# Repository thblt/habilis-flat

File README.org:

#+TITLE: Yet another keyboard

A keyboard, nothing exceptional.  This is mostly an intermediate step
for layout-testing the [[https://github.com/thblt/habilis][Habilis]].

Schematic and PCB (KiCad 7) are in =pcb/=, firmware lives in =fw/=.
The firmware is QMK, so should be symlinked in the correct location:

#+begin_example
ln -s ~/PATH/TO/REPO/habilis-flat/fw ~/qmk_firmware/keyboards/habilis-flat
#+end_example

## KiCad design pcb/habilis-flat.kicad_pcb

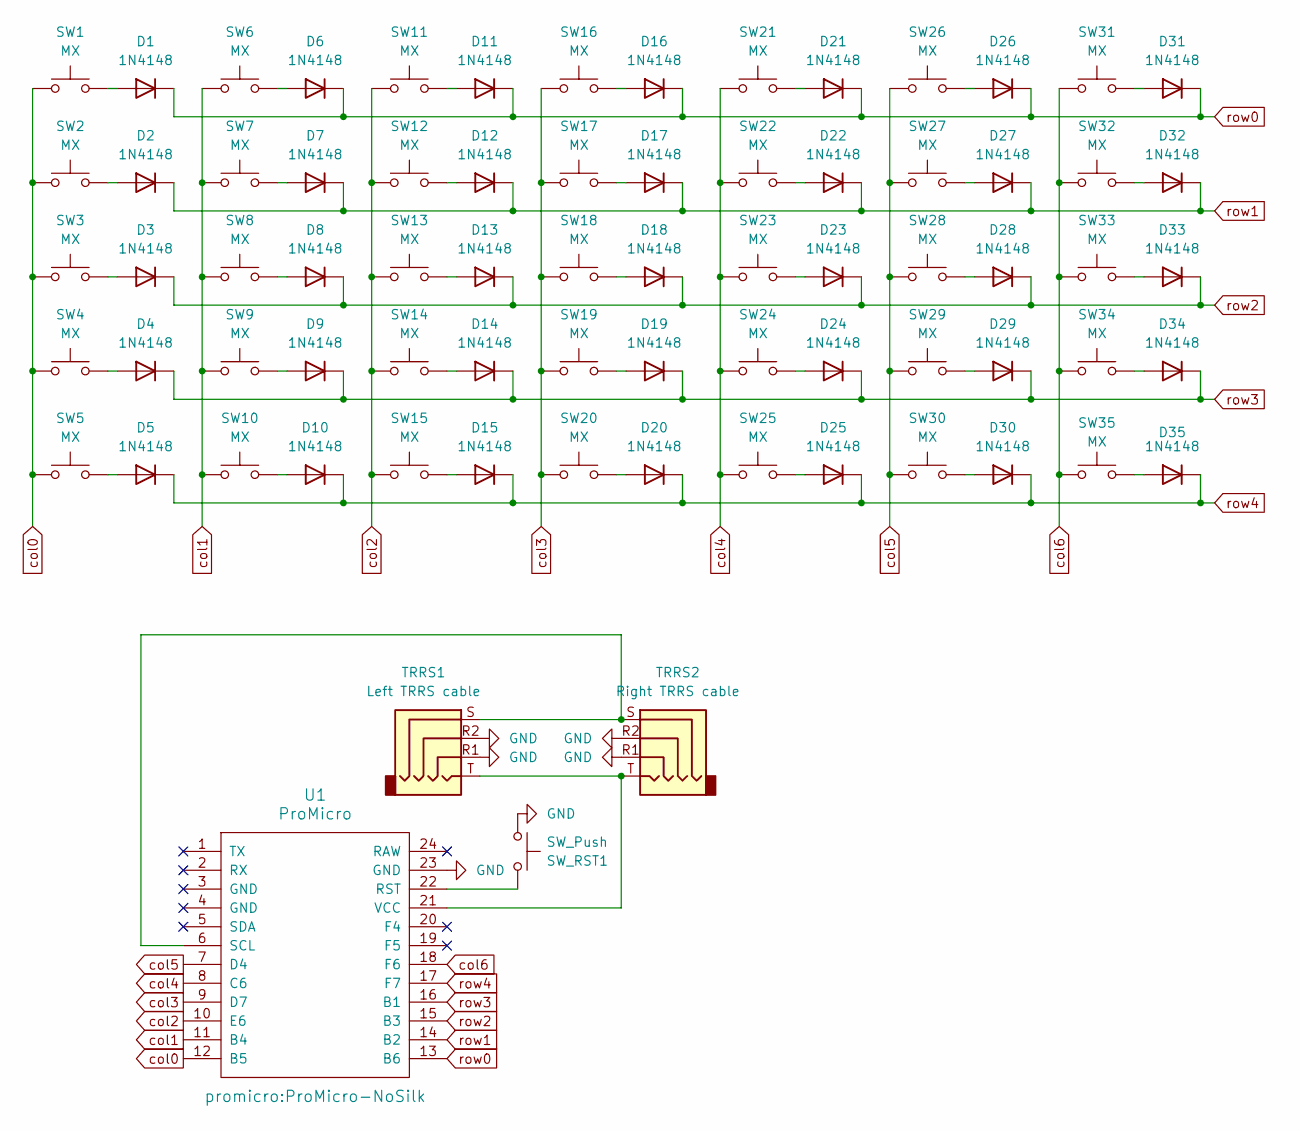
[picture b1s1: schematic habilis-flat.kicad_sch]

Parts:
D1, D2, D3, D4, D5, D6, D7, D8, D9, D10, D11, D12, D13, D14, D15, D16, D17, D18, D19, D20, D21, D22, D23, D24, D25, D26, D27, D28, D29, D30, D31, D32, D33, D34, D35: 1N4148; D_DO-35_SOD27_P7.62mm_Horizontal
SW1, SW2, SW3, SW4, SW5, SW6, SW7, SW8, SW9, SW10, SW11, SW12, SW13, SW14, SW15, SW16, SW17, SW18, SW19, SW20, SW21, SW22, SW23, SW24, SW25, SW26, SW27, SW28, SW29, SW30, SW31, SW32, SW33, SW34, SW35: MX; SW_MX_reversible_decentered
SW_RST1: SW_Push; that_push_button_i_have_in_stock
TRRS1: Left TRRS cable; Jack breakout board
TRRS2: Right TRRS cable; Jack breakout board
U1: ProMicro; ProMicro-NoSilk

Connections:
GND: SW_RST1.2, TRRS1.R1, TRRS1.R2, TRRS2.R1, TRRS2.R2, U1.23 (GND)
unnamed: D1.2 (A), SW1.1
unnamed: D2.2 (A), SW2.1
unnamed: D3.2 (A), SW3.1
unnamed: D4.2 (A), SW4.1
unnamed: D5.2 (A), SW5.1
unnamed: D6.2 (A), SW6.1
unnamed: D7.2 (A), SW7.1
unnamed: D8.2 (A), SW8.1
unnamed: D9.2 (A), SW9.1
unnamed: D10.2 (A), SW10.1
unnamed: D11.2 (A), SW11.1
unnamed: D12.2 (A), SW12.1
unnamed: D13.2 (A), SW13.1
unnamed: D14.2 (A), SW14.1
unnamed: D15.2 (A), SW15.1
unnamed: D16.2 (A), SW16.1
unnamed: D17.2 (A), SW17.1
unnamed: D18.2 (A), SW18.1
unnamed: D19.2 (A), SW19.1
unnamed: D20.2 (A), SW20.1
unnamed: D21.2 (A), SW21.1
unnamed: D22.2 (A), SW22.1
unnamed: D23.2 (A), SW23.1
unnamed: D24.2 (A), SW24.1
unnamed: D25.2 (A), SW25.1
unnamed: D26.2 (A), SW26.1
unnamed: D27.2 (A), SW27.1
unnamed: D28.2 (A), SW28.1
unnamed: D29.2 (A), SW29.1
unnamed: D30.2 (A), SW30.1
unnamed: D31.2 (A), SW31.1
unnamed: D32.2 (A), SW32.1
unnamed: D33.2 (A), SW33.2
unnamed: D34.2 (A), SW34.1
unnamed: D35.2 (A), SW35.1
unnamed: SW_RST1.1, U1.22 (RST)
unnamed: TRRS1.S, TRRS2.S, U1.6 (SCL)
unnamed: TRRS1.T, TRRS2.T, U1.21 (VCC)
col0: SW1.2, SW2.2, SW3.2, SW4.2, SW5.2, U1.12 (B5)
col1: SW6.2, SW7.2, SW8.2, SW9.2, SW10.2, U1.11 (B4)
col2: SW11.2, SW12.2, SW13.2, SW14.2, SW15.2, U1.10 (E6)
col3: SW16.2, SW17.2, SW18.2, SW19.2, SW20.2, U1.9 (D7)
col4: SW21.2, SW22.2, SW23.2, SW24.2, SW25.2, U1.8 (C6)
col5: SW26.2, SW27.2, SW28.2, SW29.2, SW30.2, U1.7 (D4)
col6: SW31.2, SW32.2, SW33.1, SW34.2, SW35.2, U1.18 (F6)
row0: D1.1 (K), D6.1 (K), D11.1 (K), D16.1 (K), D21.1 (K), D26.1 (K), D31.1 (K), U1.13 (B6)
row1: D2.1 (K), D7.1 (K), D12.1 (K), D17.1 (K), D22.1 (K), D27.1 (K), D32.1 (K), U1.14 (B2)
row2: D3.1 (K), D8.1 (K), D13.1 (K), D18.1 (K), D23.1 (K), D28.1 (K), D33.1 (K), U1.15 (B3)
row3: D4.1 (K), D9.1 (K), D14.1 (K), D19.1 (K), D24.1 (K), D29.1 (K), D34.1 (K), U1.16 (B1)
row4: D5.1 (K), D10.1 (K), D15.1 (K), D20.1 (K), D25.1 (K), D30.1 (K), D35.1 (K), U1.17 (F7)

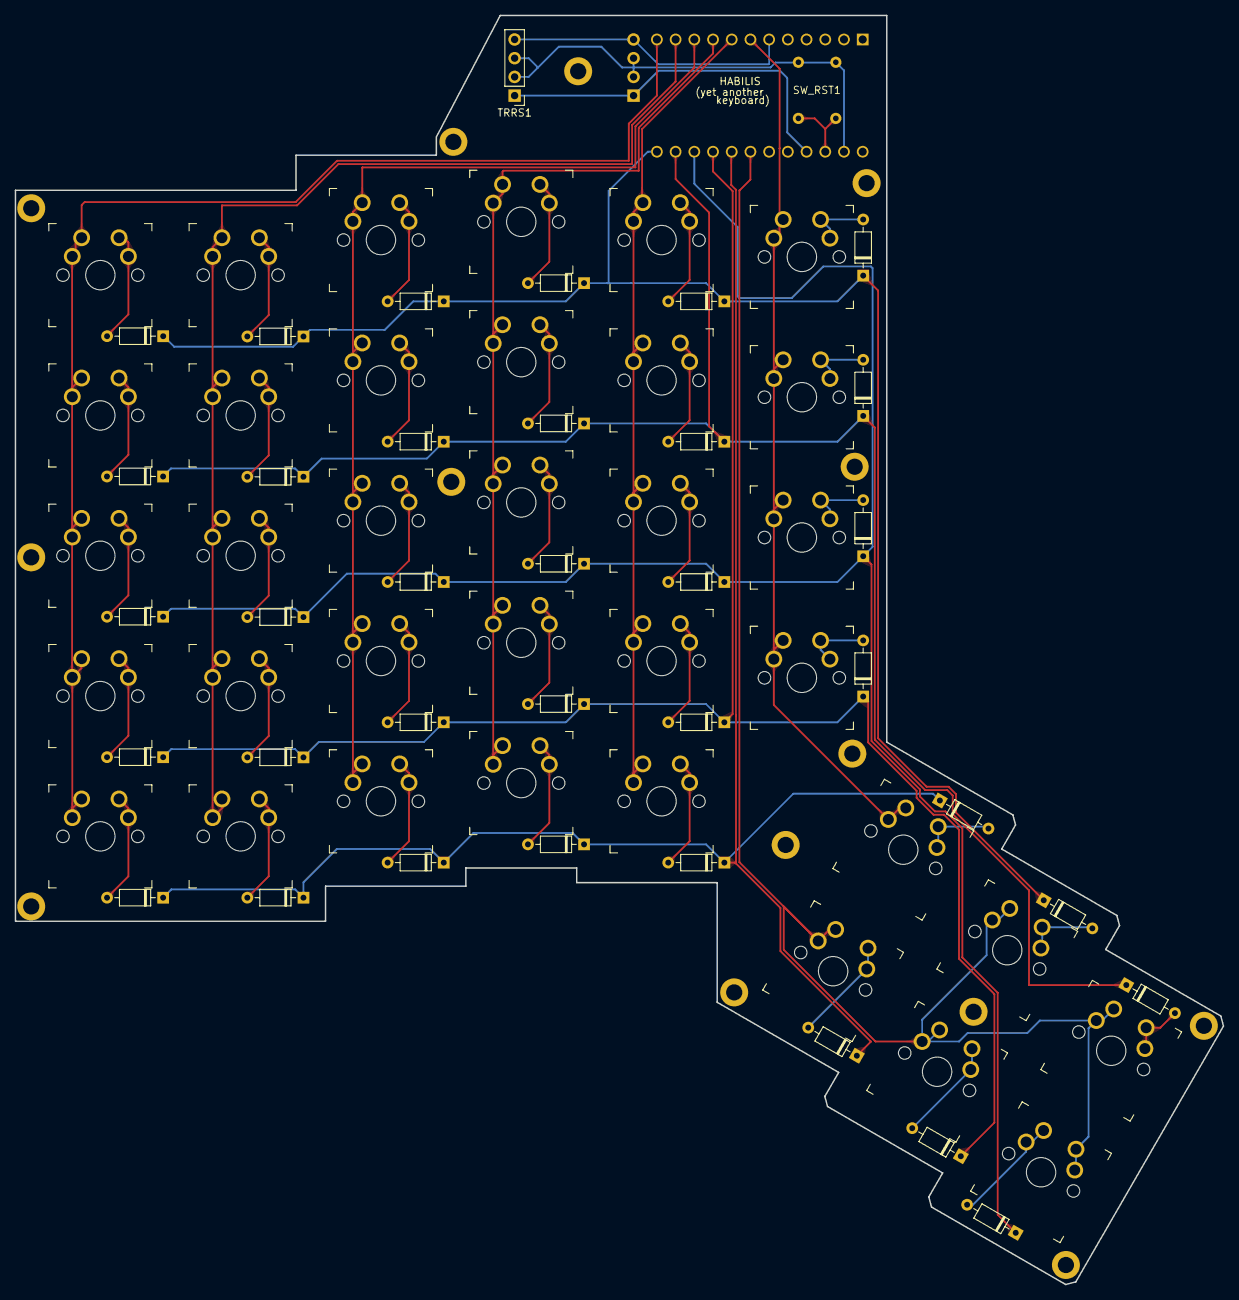
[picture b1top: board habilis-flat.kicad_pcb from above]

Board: 2 copper layers, 164.0 x 172.3 mm, 75 parts (1 on the bottom side), 51 nets.

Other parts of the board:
REFe: MountingHole_2.2mm_M2_DIN965_Pad_NO_Silkscreem

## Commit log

2023-10-31 Initial version
2023-11-01 Revision 1
2023-11-01 Remove drill files
2023-11-01 Ignore more things
2023-11-02 Revision 2
2023-11-03 Update ignore rules
2023-11-04 Ignore KiCAD lockfiles
2023-11-04 Put reset switch on the opposite side
2023-11-04 Replace MX footprint with reversible version
2023-11-04 Cleanup some tracks
2023-11-04 Use GitHub's .gitignore
2023-11-07 Redraw board shape, fix spacing mistakes
2023-11-07 Update board profile file
2023-11-07 Add silkscreen signature
2023-11-07 Ignore *.lck
2023-11-07 Restore fp-lib-table
2023-11-09 Make profile shape sharper
2023-11-09 Make profile shape even sharper
2023-11-09 Update fabrication export parameters
2023-11-11 Add mounting holes, simplify silkscreen
2023-11-11 Duplicate TRRS header
2023-11-11 Silkscreen cleanup
2023-11-11 Add teardrops
2023-11-11 Make board a bit less sharp
2023-11-11 Add firmware
2023-11-11 Add README
2023-11-11 Simplify schematic, update diode footprint reference
2023-11-11 Fix jack connectors references
2023-11-11 Update PCB
2023-11-11 Create MX hole footprint for plate
2023-11-13 Align keymap
2023-11-13 Realign thumb cluster keys
2023-11-15 Renumber rows and columns to start at 0
2023-11-15 Move copyright to a nicer place
2023-11-15 Ignore #auto_saved_files#
2023-11-15 Restore mounting holes
2023-11-15 Update teardrops
2023-11-18 Simplify schematic, pacify ERC
2023-11-18 Add more mounting holes
2023-11-19 Replace reset button fp with one I have at hand
2024-01-05 Fix footprint for reset button
2024-01-06 Restore teardrops

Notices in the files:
pcb/habilis-flat.kicad_pcb:
© Thibault Polge
